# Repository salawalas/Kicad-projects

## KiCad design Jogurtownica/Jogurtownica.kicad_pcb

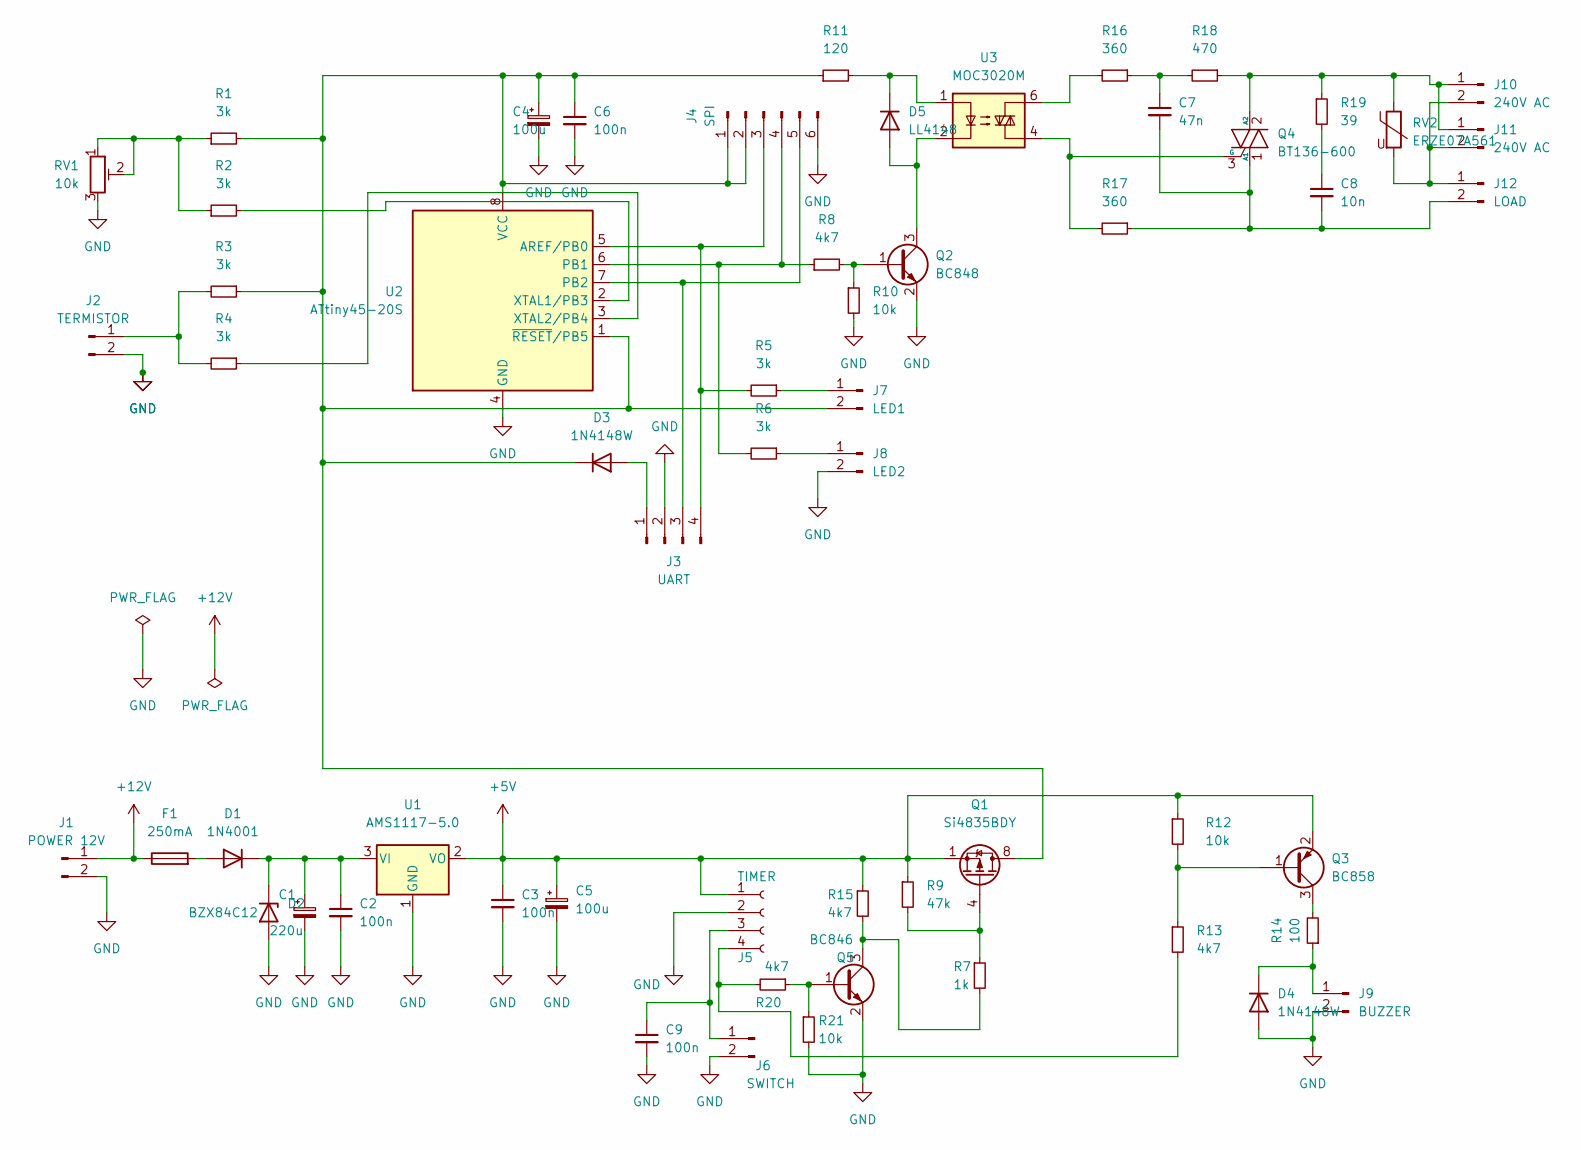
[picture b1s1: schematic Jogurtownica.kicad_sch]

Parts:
C1: 220u; CP_Radial_D8.0mm_P3.50mm
C2, C3, C6, C9: 100n; C_0805_2012Metric
C4, C5: 100u; CP_Radial_D5.0mm_P2.50mm
C7: 47n; C_Rect_L10.3mm_W5.0mm_P7.50mm_MKS4
C8: 10n; C_Rect_L10.3mm_W5.0mm_P7.50mm_MKS4
D1: 1N4001; D_MELF
D2: BZX84C12; D_MELF
D3, D4: 1N4148W; D_MiniMELF
D5: LL4148; D_MiniMELF
F1: 250mA; Fuse_2010_5025Metric
J1: POWER 12V; Molex_KK-254_AE-6410-02A_1x02_P2.54mm_Vertical
J2: TERMISTOR; JST_PH_B2B-PH-K_1x02_P2.00mm_Vertical
J3: UART; PinHeader_1x04_P2.54mm_Vertical
J4: SPI; PinHeader_1x06_P2.54mm_Vertical
J5: TIMER; PinSocket_1x04_P2.54mm_Vertical
J6: SWITCH; JST_PH_B2B-PH-K_1x02_P2.00mm_Vertical
J7: LED1; JST_PH_B2B-PH-K_1x02_P2.00mm_Vertical
J8: LED2; JST_PH_B2B-PH-K_1x02_P2.00mm_Vertical
J9: BUZZER; JST_PH_B2B-PH-K_1x02_P2.00mm_Vertical
J10, J11: 240V AC; TE_826576-2_1x02_P3.96mm_Vertical
J12: LOAD; JST_VH_B2PS-VH_1x02_P3.96mm_Horizontal
Q1: Si4835BDY; SOIC-8_3.9x4.9mm_P1.27mm
Q2: BC848; SOT-23
Q3: BC858; SOT-23
Q4: BT136-600; TO-220-3_Vertical
Q5: BC846; SOT-23
R1, R2, R3, R4, R5, R6: 3k; R_0805_2012Metric
R7: 1k; R_0805_2012Metric
R8, R13, R15, R20: 4k7; R_0805_2012Metric
R9: 47k; R_0805_2012Metric
R10, R12, R21: 10k; R_0805_2012Metric
R11: 120; R_0805_2012Metric
R14: 100; R_0805_2012Metric
R16, R17: 360; R_1206_3216Metric
R18: 470; R_1206_3216Metric
R19: 39; R_1206_3216Metric
RV1: 10k; Potentiometer_Bourns_3299X_Horizontal
RV2: ERZE07A561; RV_Disc_D12mm_W4.3mm_P7.5mm
U1: AMS1117-5.0; SOT-223-3_TabPin2
U2: ATtiny45-20S; DIP-8_W7.62mm
U3: MOC3020M; DIP-6_W7.62mm

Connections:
+5V: C3.1, C5.1, J5.1, Q1.1 (S), Q1.2 (S), Q1.3 (S), Q3.2 (E), R9.1, R12.1, R15.1, U1.2 (VO)
+12V: F1.1, J1.1
GND: C1.2, C2.2, C3.2, C4.2, C5.2, C6.2, C9.2, D2.2 (A), D4.2 (A), J1.2, J2.2, J3.2, J4.6, J5.2, J6.2, J8.2, J9.2, Q2.2 (E), Q5.2 (E), R10.2, R21.2, RV1.3, U1.1 (GND), U2.4 (GND)
unnamed: C1.1, C2.1, D1.1 (K), D2.1 (K), U1.3 (VI)
unnamed: C4.1, C6.1, D3.1 (K), J4.1, J4.2, J7.2, Q1.5 (D), Q1.6 (D), Q1.7 (D), Q1.8 (D), R1.2, R3.1, R11.1, U2.1 (~RESET/PB5), U2.8 (VCC)
unnamed: C7.1, R16.1, R18.2
unnamed: C7.2, C8.2, J12.2, Q4.1 (A1), R17.1
unnamed: C8.1, R19.2
unnamed: D1.2 (A), F1.2
unnamed: D3.2 (A), J3.1
unnamed: D4.1 (K), J9.1, R14.1
unnamed: J2.1, R3.2, R4.2
unnamed: J3.3, J4.5, U2.7 (PB2)
unnamed: J3.4, J4.3, R5.2, U2.5 (AREF/PB0)
unnamed: J4.4, R6.2, R8.1, U2.6 (PB1)
unnamed: C9.1, J5.3, J6.1
unnamed: J5.4, R13.2, R20.2
unnamed: J7.1, R5.1
unnamed: J8.1, R6.1
unnamed: J10.1, J11.1, Q4.2 (A2), R18.1, R19.1, RV2.1
unnamed: J10.2, J11.2, J12.1, RV2.2
unnamed: Q1.4 (G), R7.1, R9.2
unnamed: Q2.1 (B), R8.2, R10.1
unnamed: D5.2 (A), Q2.3 (C), U3.2
unnamed: Q3.1 (B), R12.2, R13.1
unnamed: Q3.3 (C), R14.2
unnamed: Q4.3 (G), R17.2, U3.4
unnamed: Q5.1 (B), R20.1, R21.1
unnamed: Q5.3 (C), R7.2, R15.2
unnamed: R1.1, R2.1, RV1.1, RV1.2
unnamed: R2.2, U2.2 (XTAL1/PB3)
unnamed: R4.1, U2.3 (XTAL2/PB4)
unnamed: D5.1 (K), R11.2, U3.1
unnamed: R16.2, U3.6

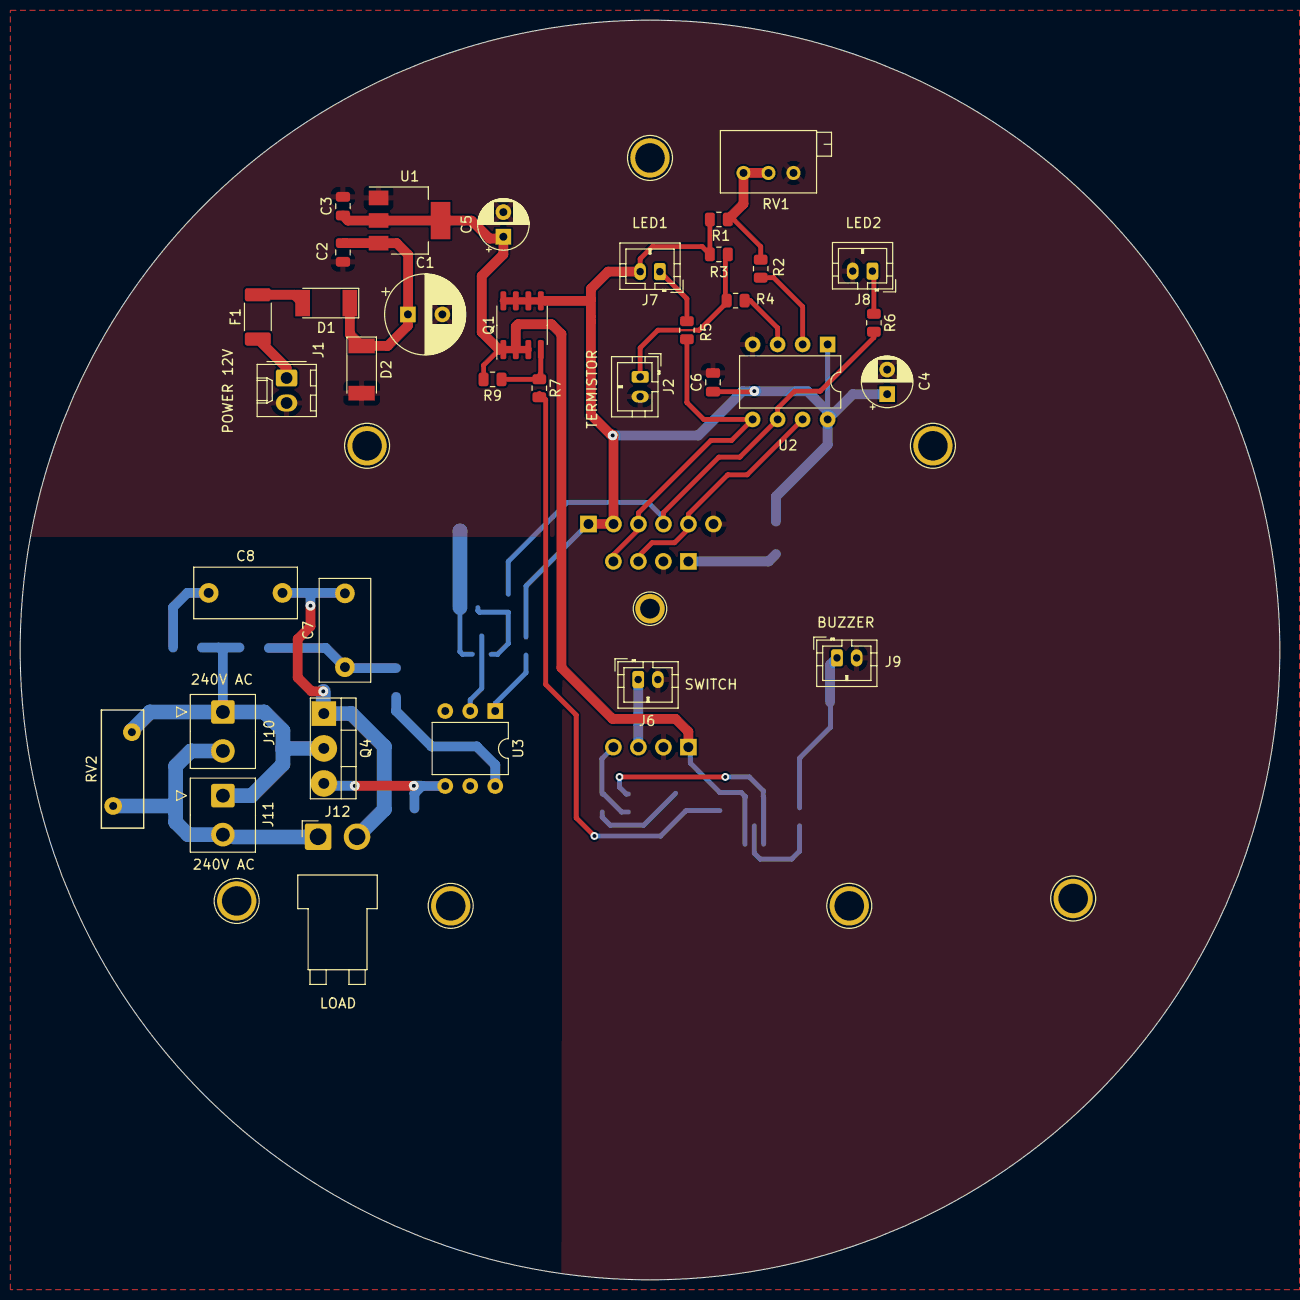
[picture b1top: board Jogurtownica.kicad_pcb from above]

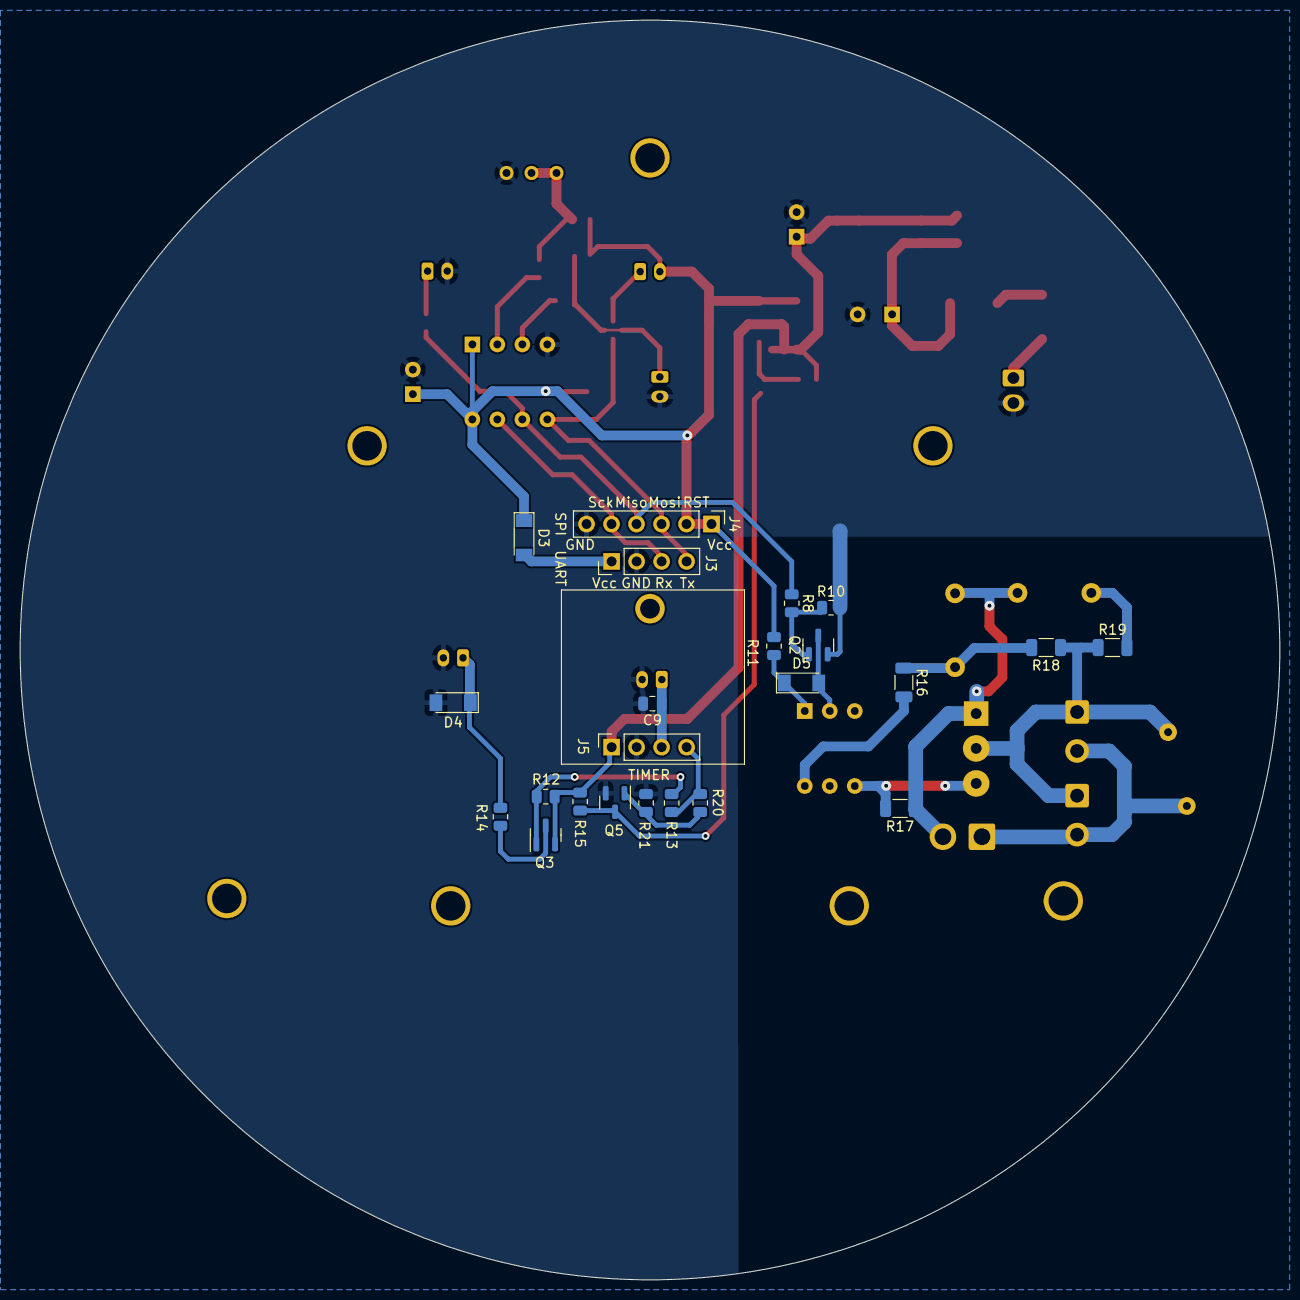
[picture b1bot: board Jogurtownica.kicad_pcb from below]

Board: 2 copper layers, 128.0 x 128.0 mm, 58 parts (23 on the bottom side), 34 nets.

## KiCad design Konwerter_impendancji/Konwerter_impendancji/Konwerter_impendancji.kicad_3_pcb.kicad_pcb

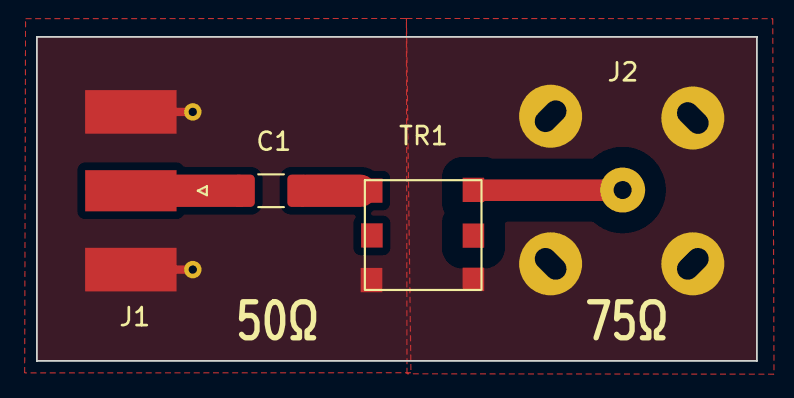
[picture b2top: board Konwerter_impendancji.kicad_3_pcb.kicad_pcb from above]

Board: 2 copper layers, 40.0 x 18.0 mm, 4 parts (0 on the bottom side), 4 nets.

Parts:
C1: 72p; C_1206_3216Metric
J1: Conn_Coaxial; SMA_Molex_73251-1153_EdgeMount_Horizontal
J2: Coax_F_female_poziomy
TR1: ADT1.5-2; Tranformator_Coilcraft_TTWB1015L

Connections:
GND: J1.2 (Ext), J2.2, TR1.3, TR1.4
unnamed: C1.1, TR1.1
unnamed: J2.1, TR1.6
unnamed: C1.2, J1.1 (In)

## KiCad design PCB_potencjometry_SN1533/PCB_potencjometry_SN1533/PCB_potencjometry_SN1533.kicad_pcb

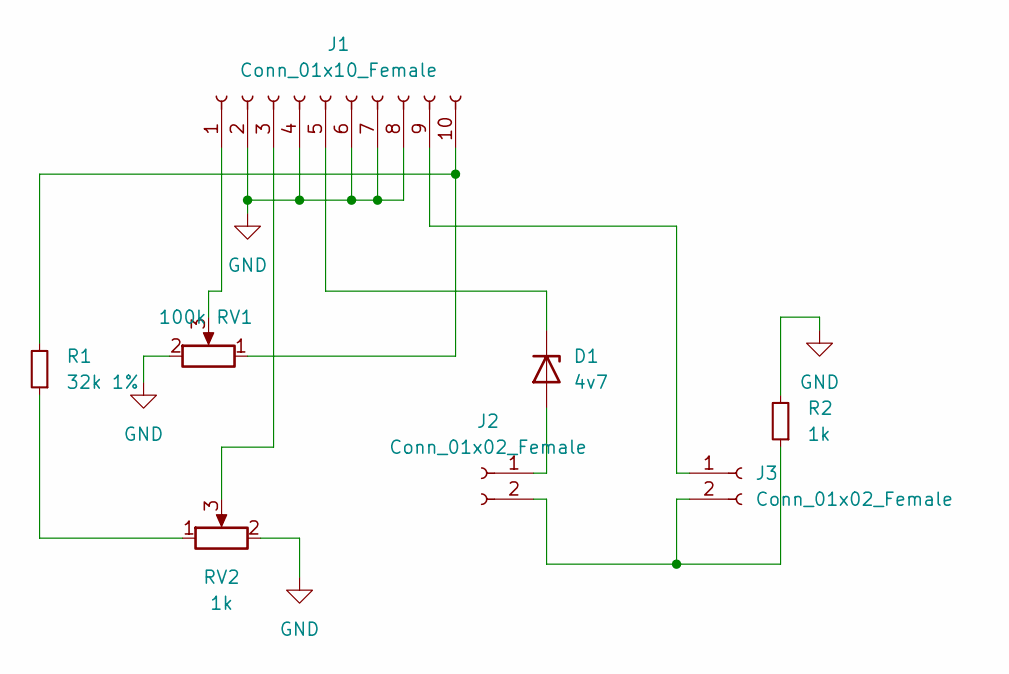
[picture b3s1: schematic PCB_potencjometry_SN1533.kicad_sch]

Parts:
D1: 4v7; D_DO-34_SOD68_P10.16mm_Horizontal
J1: Conn_01x10_Female; PinHeader_1x10_P2.54mm_Vertical
J2, J3: Conn_01x02_Female; JST_PH_B2B-PH-K_1x02_P2.00mm_Vertical
R1: 32k 1%; R_Axial_DIN0411_L9.9mm_D3.6mm_P12.70mm_Horizontal
R2: 1k; R_Axial_DIN0411_L9.9mm_D3.6mm_P12.70mm_Horizontal
RV1: 100k; Potencjometr_wieloobrotowy_Bourns
RV2: 1k; Potencjometr_wieloobrotowy_Bourns

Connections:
GND: J1.2, J1.4, J1.6, J1.7, J1.8, R2.2, RV1.2, RV2.2
unnamed: D1.1 (K), J1.5
unnamed: D1.2 (A), J2.1
unnamed: J1.1, RV1.3
unnamed: J1.3, RV2.3
unnamed: J1.9, J3.1
unnamed: J1.10, R1.2, RV1.1
unnamed: R1.1, RV2.1
unnamed: J2.2, J3.2, R2.1

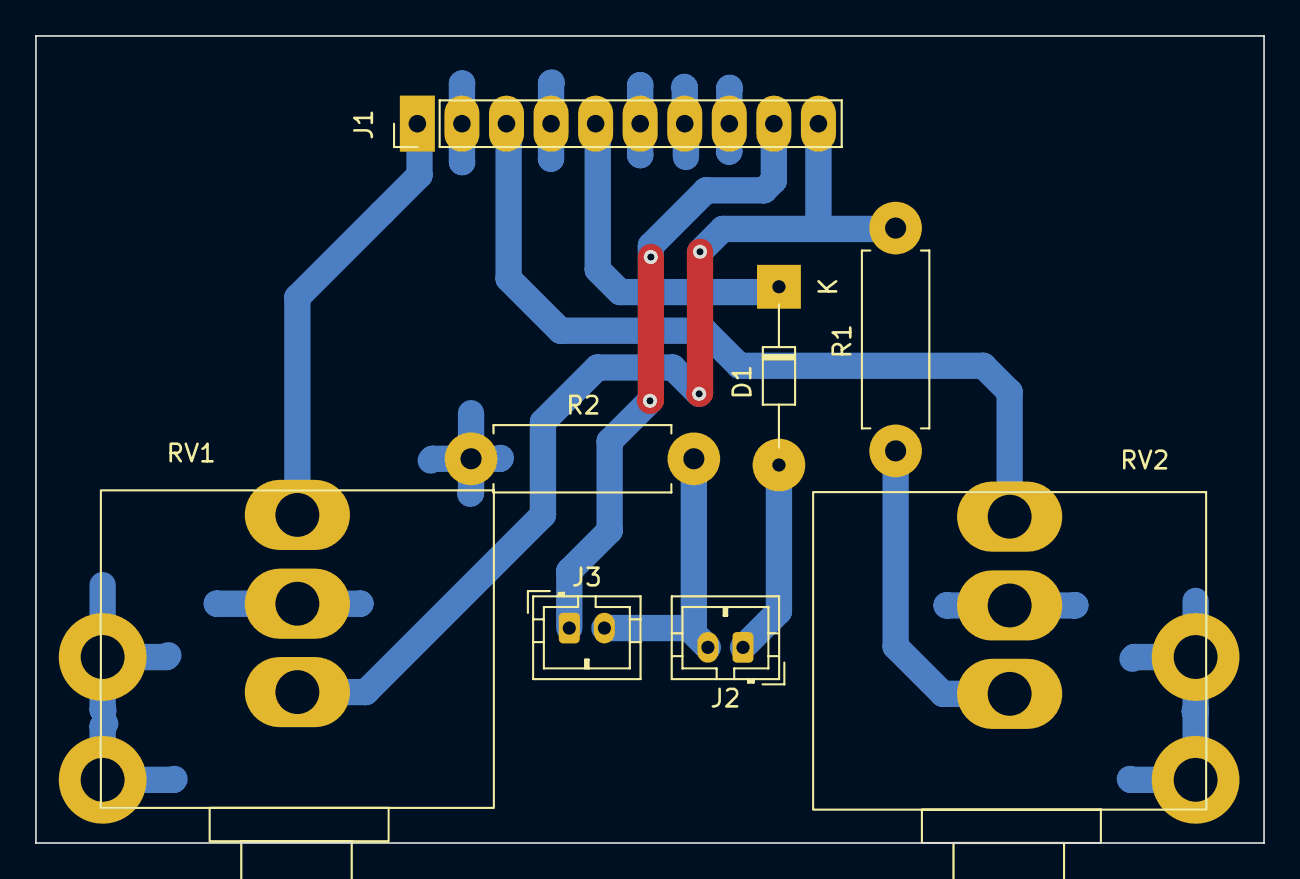
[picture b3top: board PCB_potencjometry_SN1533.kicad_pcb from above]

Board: 2 copper layers, 70.0 x 46.0 mm, 8 parts (0 on the bottom side), 9 nets.

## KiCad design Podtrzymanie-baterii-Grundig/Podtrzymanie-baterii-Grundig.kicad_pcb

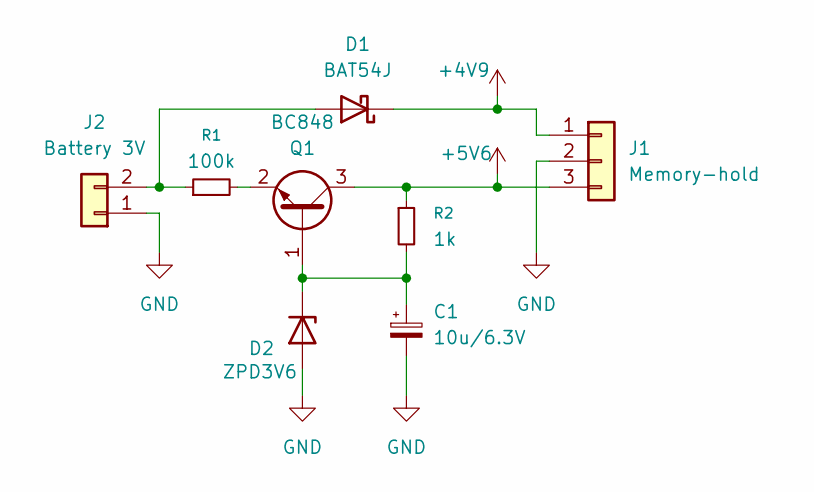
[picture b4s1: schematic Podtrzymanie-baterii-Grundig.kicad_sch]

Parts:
C1: 10u/6.3V; CP_Radial_D4.0mm_P2.00mm
D1: BAT54J; D_SOD-323F
D2: ZPD3V6; D_DO-35_SOD27_P5.08mm_Vertical_AnodeUp
J1: Memory-hold; PinHeader_1x03_P2.54mm_Vertical
J2: Battery 3V; PinHeader_1x02_P2.54mm_Vertical
Q1: BC848; SOT-23
R1: 100k; R_1206_3216Metric
R2: 1k; R_1206_3216Metric

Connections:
+4V9: D1.1 (K), J1.1
+5V6: J1.3, Q1.3 (C), R2.1
GND: C1.2, D2.2 (A), J1.2, J2.1
unnamed: D1.2 (A), J2.2, R1.1
unnamed: C1.1, D2.1 (K), Q1.1 (B), R2.2
unnamed: Q1.2 (E), R1.2

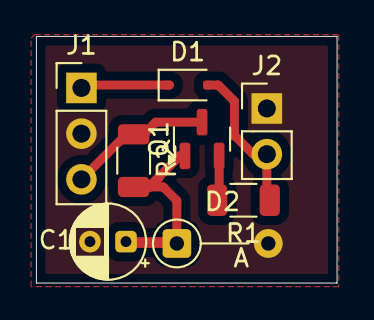
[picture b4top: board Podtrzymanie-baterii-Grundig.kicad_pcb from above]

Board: 2 copper layers, 16.7 x 13.7 mm, 8 parts (0 on the bottom side), 6 nets.

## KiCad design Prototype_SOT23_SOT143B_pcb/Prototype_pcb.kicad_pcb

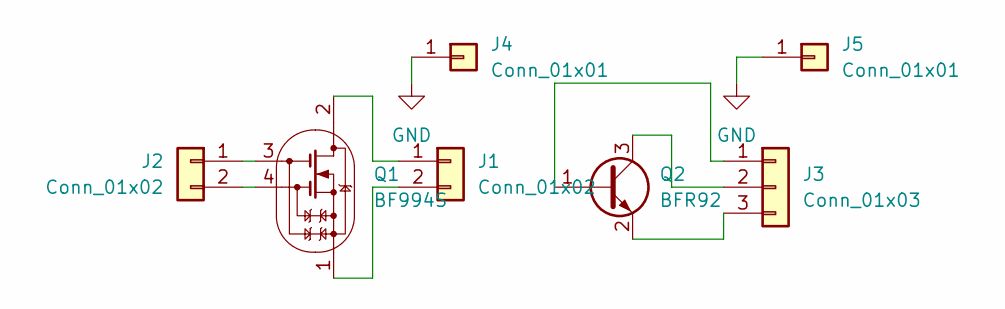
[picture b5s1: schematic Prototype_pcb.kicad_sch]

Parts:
J1, J2: Conn_01x02; PinHeader_1x02_P2.54mm_Vertical
J3: Conn_01x03; PinHeader_1x03_P2.54mm_Vertical
J4, J5: Conn_01x01; PinHeader_1x01_P2.54mm_Vertical
Q1: BF994S; SOT-143
Q2: BFR92; SOT-23

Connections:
GND: J4.1, J5.1
unnamed: J1.1, Q1.2 (D)
unnamed: J1.2, Q1.1 (S)
unnamed: J2.1, Q1.3 (G2)
unnamed: J2.2, Q1.4 (G1)
unnamed: J3.1, Q2.1 (B)
unnamed: J3.2, Q2.3 (C)
unnamed: J3.3, Q2.2 (E)

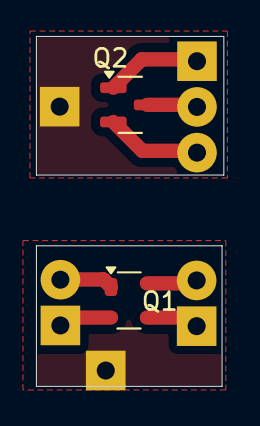
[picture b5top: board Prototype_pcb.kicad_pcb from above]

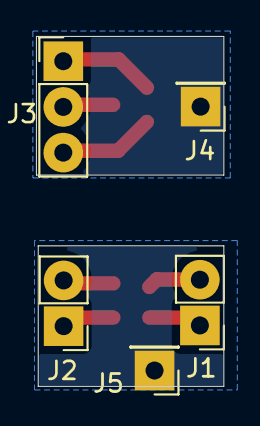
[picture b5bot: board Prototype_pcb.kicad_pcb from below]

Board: 2 copper layers, 10.4 x 19.4 mm, 7 parts (5 on the bottom side), 8 nets.

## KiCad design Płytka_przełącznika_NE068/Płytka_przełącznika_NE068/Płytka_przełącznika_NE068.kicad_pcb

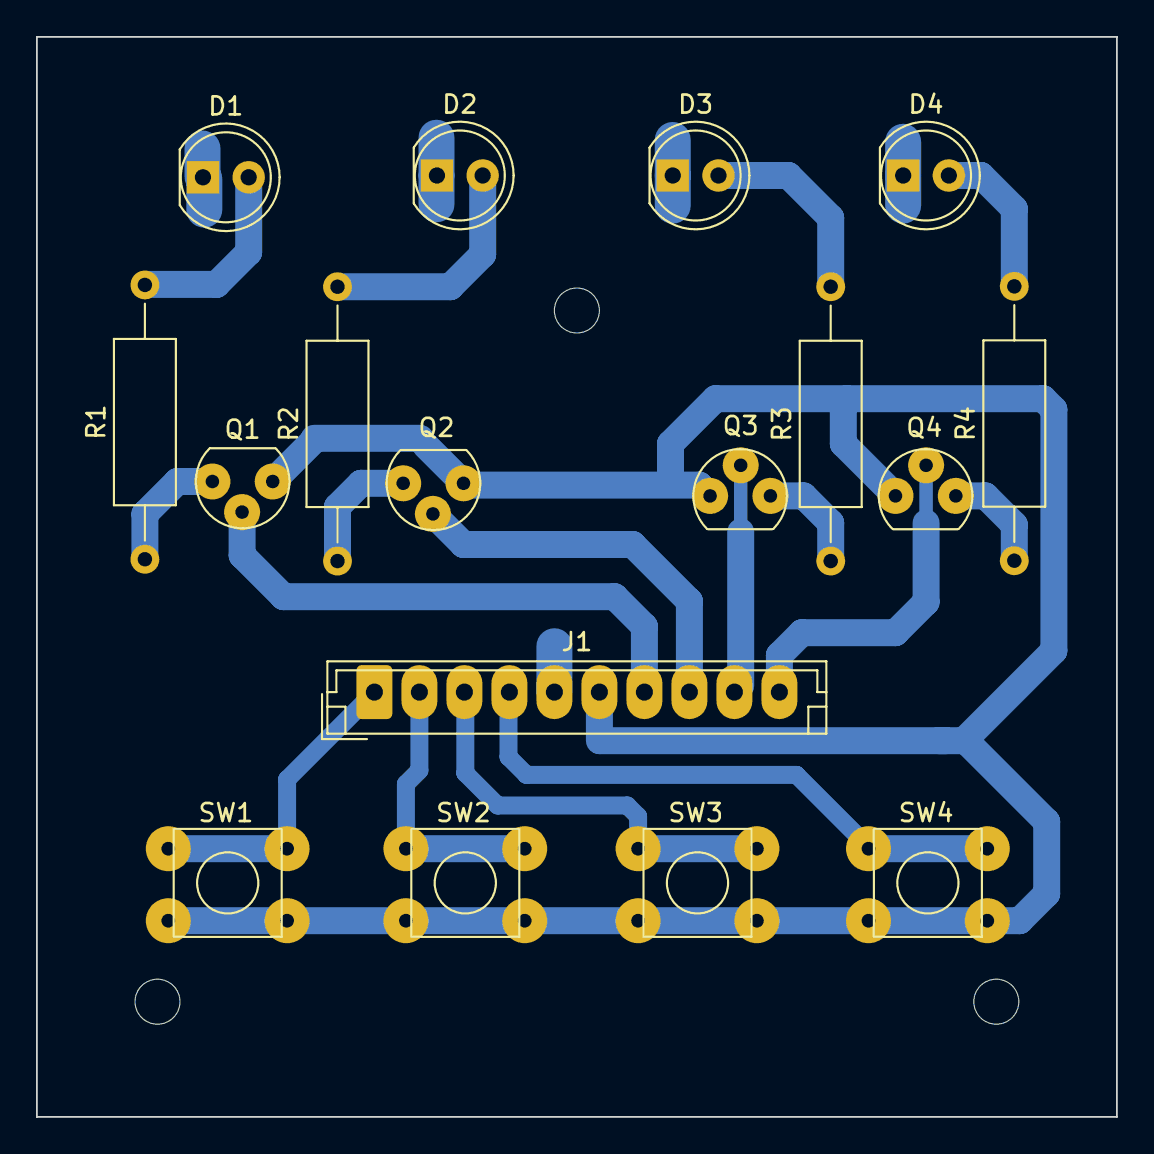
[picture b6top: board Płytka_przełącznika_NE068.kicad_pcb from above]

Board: 2 copper layers, 60.0 x 60.0 mm, 17 parts (0 on the bottom side), 18 nets.

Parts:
D1, D2, D3, D4: LED_Small; LED_D5.0mm_Clear
J1: Conn_01x10_Female; JST_EH_B10B-EH-A_1x10_P2.50mm_Vertical
Q1, Q2, Q3, Q4: BC237; TO-92
R1, R2, R3, R4: 820; R_Axial_DIN0309_L9.0mm_D3.2mm_P15.24mm_Horizontal
SW1, SW2, SW3, SW4: SW_MEC_5E; Tact_switch 6x6

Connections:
GND: D1.1 (K), D2.1 (K), D3.1 (K), D4.1 (K), J1.5
unnamed: D1.2 (A), R1.2
unnamed: D2.2 (A), R2.2
unnamed: D3.2 (A), R3.2
unnamed: D4.2 (A), R4.2
unnamed: J1.1, SW1.3 (K), SW1.4 (A)
unnamed: J1.2, SW2.3 (K), SW2.4 (A)
unnamed: J1.3, SW3.3 (K), SW3.4 (A)
unnamed: J1.4, SW4.3 (K), SW4.4 (A)
unnamed: J1.6, Q1.1 (C), Q2.1 (C), Q3.1 (C), Q4.1 (C), SW1.1, SW1.2, SW2.1, SW2.2, SW3.1, SW3.2, SW4.1, SW4.2
unnamed: J1.7, Q1.2 (B)
unnamed: J1.8, Q2.2 (B)
unnamed: J1.9, Q3.2 (B)
unnamed: J1.10, Q4.2 (B)
unnamed: Q1.3 (E), R1.1
unnamed: Q2.3 (E), R2.1
unnamed: Q3.3 (E), R3.1
unnamed: Q4.3 (E), R4.1
